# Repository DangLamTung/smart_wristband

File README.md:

# smart_wristband
 Smart Wristband

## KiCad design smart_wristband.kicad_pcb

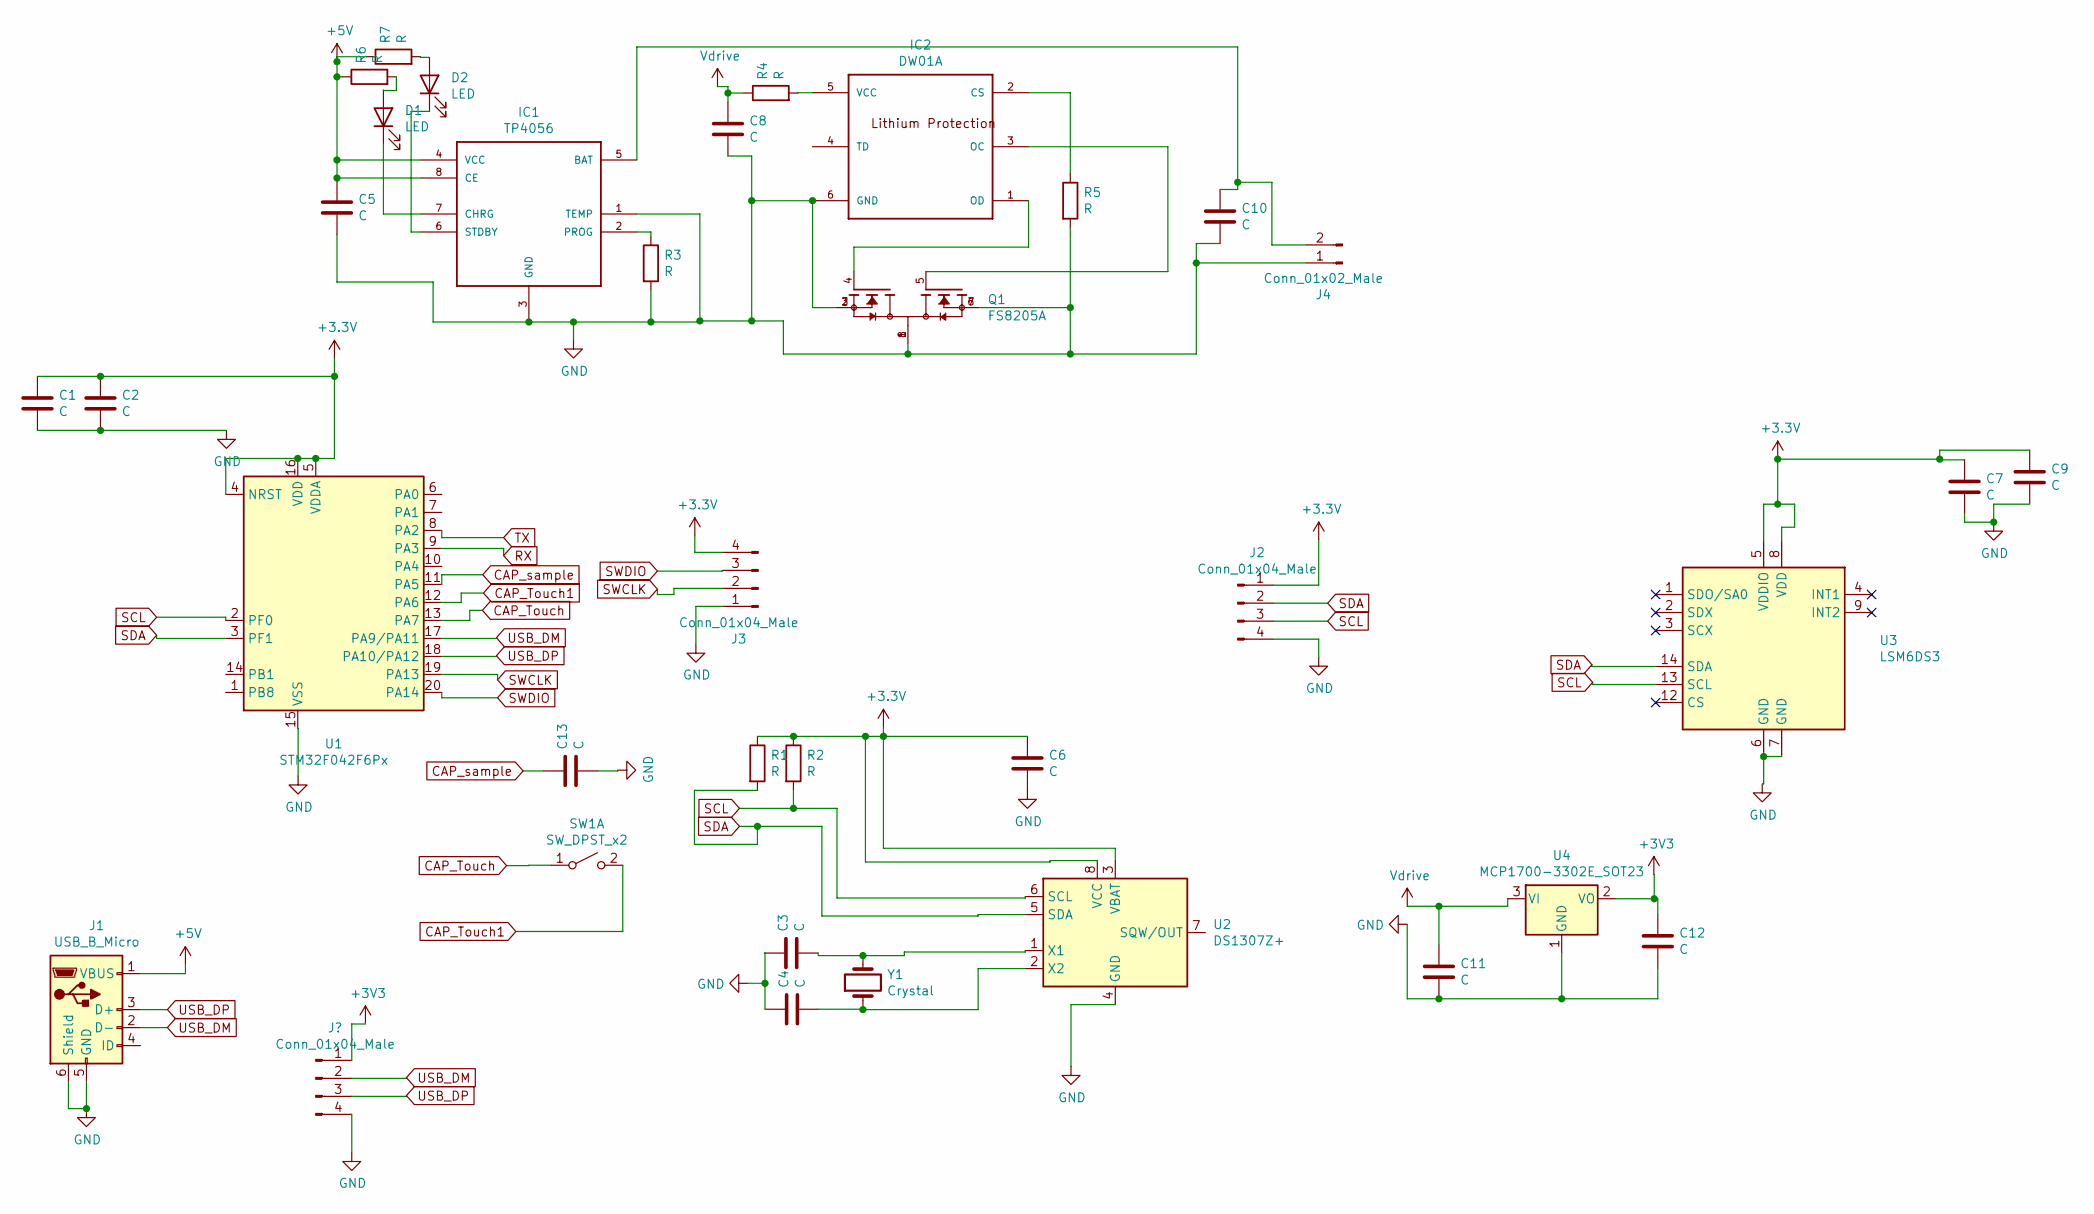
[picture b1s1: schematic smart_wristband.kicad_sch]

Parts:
C1, C2, C6, C10: C; C_0402_1005Metric
C3, C4, C5, C8, C13: C; C_0603_1608Metric_Pad1.05x0.95mm_HandSolder
C7, C9: C
C11, C12: C; C_0603_1608Metric
D1, D2: LED; LED_0603_1608Metric
IC1: TP4056; Diodes_PSOP-8
IC2: DW01A; SOT23-6
J1: USB_B_Micro; USB_Micro-B_Amphenol_10104110_Horizontal
J2: Conn_01x04_Male; PinSocket_1x04_P2.54mm_Vertical
J3: Conn_01x04_Male; JST_SH_BM04B-SRSS-TB_1x04-1MP_P1.00mm_Vertical
J4: Conn_01x02_Male; PinSocket_1x02_P2.00mm_Vertical
Q1: FS8205A; SOP65P640X120-8N
R1, R2, R3, R4, R5, R6, R7: R; R_0603_1608Metric
SW1: SW_DPST_x2; TouchSlider-2_10x10mm
U1: STM32F042F6Px; TSSOP-20_4.4x6.5mm_P0.65mm
U2: DS1307Z+; SOIC-8_3.9x4.9mm_P1.27mm
U3: LSM6DS3; LGA-14_3x2.5mm_P0.5mm_LayoutBorder3x4y
U4: MCP1700-3302E_SOT23; SOT-23
Y1: Crystal; Crystal_C26-LF_D2.1mm_L6.5mm_Vertical

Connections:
+5V: C5.1, IC1.4 (VCC), IC1.8 (CE), J1.1 (VBUS), R6.1, R7.1
CAP_Touch: SW1.1 (A), U1.13 (PA7)
CAP_Touch1: SW1.2 (B), U1.12 (PA6)
CAP_sample: C13.1, U1.11 (PA5)
GND: C1.2, C2.2, C3.1, C4.1, C5.2, C6.2, C7.2, C8.2, C9.2, C10.2, C11.2, C12.2, C13.2, IC1.1 (TEMP), IC1.3 (GND), IC2.6 (GND), J1.5 (GND), J1.6 (Shield), J2.4, J3.1, J4.1, Q1.1, Q1.2, Q1.3, Q1.6, Q1.7, Q1.8, R3.2, R5.2, U1.15 (VSS), U2.4 (GND), U3.6 (GND), U3.7 (GND), U4.1 (GND); also elsewhere on the board
unnamed: C3.2, U2.1 (X1), Y1.2
unnamed: C4.2, U2.2 (X2), Y1.1
unnamed: C10.1, IC1.5 (BAT), J4.2
unnamed: D1.1 (K), IC1.7 (CHRG)
unnamed: D1.2 (A), R6.2
unnamed: D2.1 (K), IC1.6 (STDBY)
unnamed: D2.2 (A), R7.2
unnamed: IC1.2 (PROG), R3.1
unnamed: IC2.1 (OD), Q1.4
unnamed: IC2.2 (CS), R5.1
unnamed: IC2.3 (OC), Q1.5
unnamed: IC2.5 (VCC), R4.2
RX: U1.9 (PA3)
SCL: J2.3, R2.2, U1.2 (PF0), U2.6 (SCL), U3.13 (SCL)
SDA: J2.2, R1.2, U1.3 (PF1), U2.5 (SDA), U3.14 (SDA)
SWCLK: J3.2, U1.19 (PA13)
SWDIO: J3.3, U1.20 (PA14)
TX: U1.8 (PA2)
USB_DM: J1.2 (D-), U1.17 (PA9/PA11); also elsewhere on the board
USB_DP: J1.3 (D+), U1.18 (PA10/PA12); also elsewhere on the board
Vdrive: C8.1, C11.1, R4.1, U4.3 (VI)

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
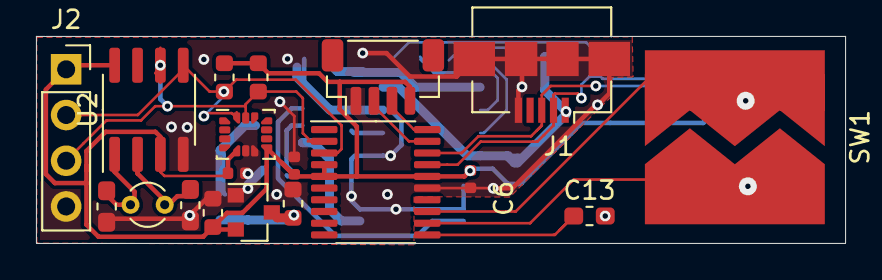
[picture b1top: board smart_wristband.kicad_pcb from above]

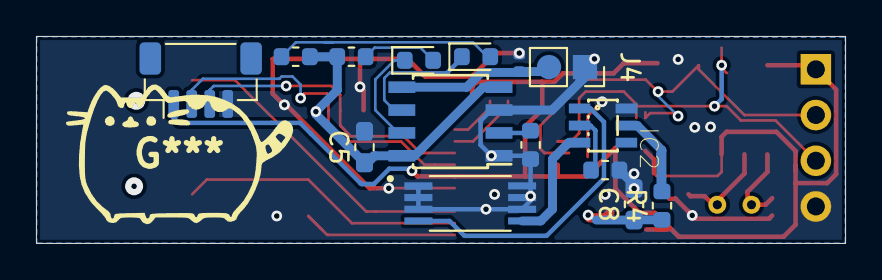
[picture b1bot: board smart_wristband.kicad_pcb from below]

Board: 2 copper layers, 45.0 x 11.5 mm, 34 parts (15 on the bottom side), 25 nets.

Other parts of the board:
J5: Conn_01x04_Male; JST_SH_BM04B-SRSS-TB_1x04-1MP_P1.00mm_Vertical

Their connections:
GND: J5.4; also elsewhere on the board
USB_DM: J5.2; also elsewhere on the board
USB_DP: J5.3; also elsewhere on the board

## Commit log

2020-09-21 add alot
